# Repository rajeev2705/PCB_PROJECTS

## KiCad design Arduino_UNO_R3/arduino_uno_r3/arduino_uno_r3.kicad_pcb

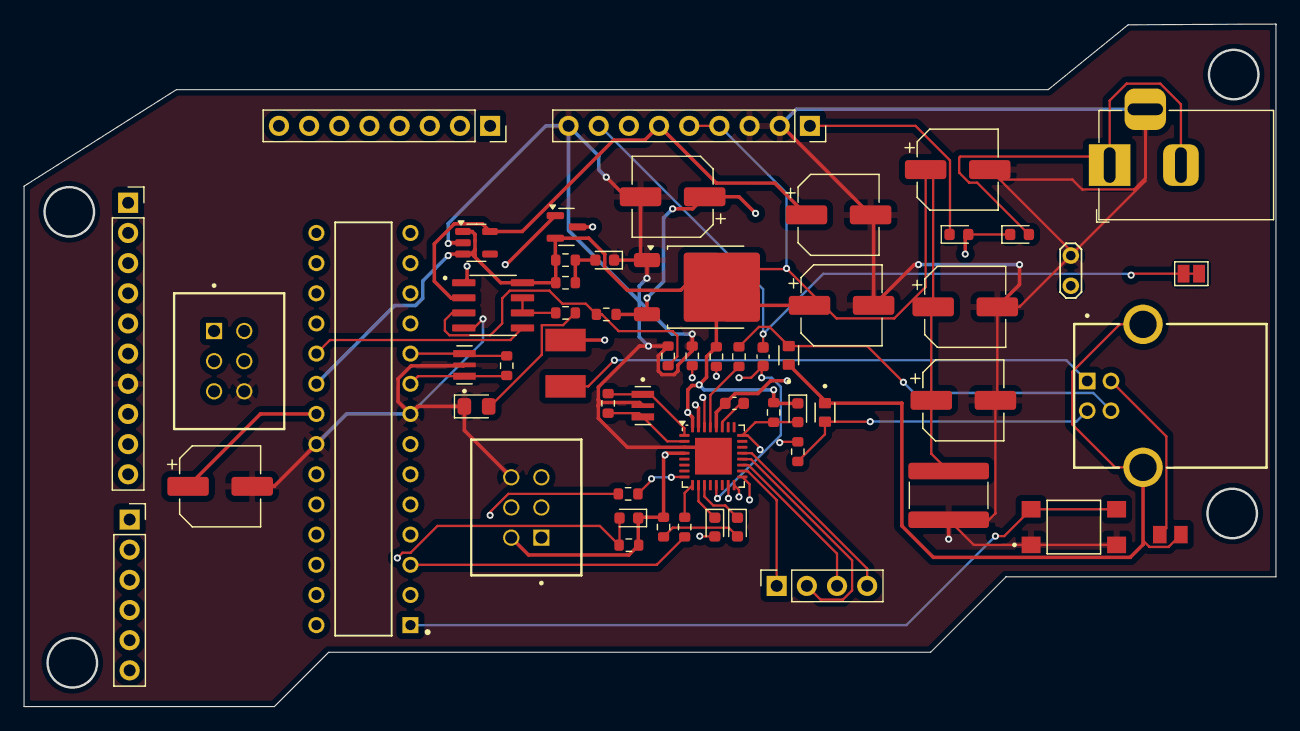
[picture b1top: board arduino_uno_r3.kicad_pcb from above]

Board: 4 copper layers, 105.4 x 57.5 mm, 58 parts (0 on the bottom side), 62 nets.

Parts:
C1, C2: 47u; CP_Elec_6.3x3
C3, C4, C9, C10: 100n; CP_Elec_6.3x3
C5: 1u; CP_Elec_6.3x3
C6: 1u; C_0603_1608Metric
C7: 100n; C_1825_4564Metric
C8: 100n; C_0603_1608Metric
D1, D3, D7, D8: D; D_0603_1608Metric
D2: GREEN ON; LED_0603_1608Metric
D4, D5: LED; LED_0603_1608Metric
D6: LED; LED_0805_2012Metric_Pad1.15x1.40mm_HandSolder
F1: MF-MSMF050-2; FUSM1812X02
FL1: BLM21SP111SH1D; BEADC2012X105N
J1: Barrel_Jack_Switch_Pin3Ring; BarrelJack_Horizontal
J2: Conn_01x09_Socket; PinSocket_1x09_P2.54mm_Vertical
J3: USB-B-S-X-X-TH-TR; SAMTEC_USB-B-S-X-X-TH-TR
J4, J6: ICSP HEADER; SAMTEC_TSS-103-03-L-D
J5: Conn_01x04_Socket; PinSocket_1x04_P2.54mm_Vertical
J7: Conn_01x08_Socket; PinSocket_1x08_P2.54mm_Vertical
J8: Conn_01x10_Socket; PinSocket_1x10_P2.54mm_Vertical
J9: Conn_01x06_Socket; PinSocket_1x06_P2.54mm_Vertical
JP1: SolderJumper_2_Open; SolderJumper-2_P1.3mm_Open_Pad1.0x1.5mm
JP2: SolderJumper_2_Open; TestPoint_2Pads_Pitch2.54mm_Drill0.8mm
Q1: FDN340P; SOT-23
R1A1, R1B1, R8, R9, R11, R12, R15, R16: 1k; R_0603_1608Metric
R3, R4, R5, R14: 10k; R_0603_1608Metric
R6, R7: 22R; R_0603_1608Metric
R10, R13: 1M; R_0603_1608Metric
RV1, RV2: CG0603MLC-05E; VARC1608X56N
S1: TL3305CF160QG; SW_TL3305CF160QG
U1: NCP1117-5.0_TO252; TO-252-2
U3: LP2985-3.3; SOT-23-5
U4: ATmega16U2-M; QFN-32-1EP_5x5mm_P0.5mm_EP3.1x3.1mm
U6: LMV358; SOIC127P599X175-8N
U7: ATMEGA328P-PU; DIP794W46P254L2967H457Q28B
Y1, Y2: CSTCE16M0V53-R0; OSC_CSTCE16M0V53-R0

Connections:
+5V: C2.1, C3.1, C4.1, C7.2, C10.1, D3.1 (K), D7.1 (K), J2.4, J2.5, J4.02, J6.02, Q1.2 (S), R1A1.2, R1B1.2, R5.2, R8.1, R9.1, R14.2, U1.2 (VO), U3.1 (VIN), U3.3 (ON/~OFF), U4.4 (VCC), U4.32 (AVCC), U6.8 (V+), U7.7 (VCC), U7.20 (AVCC)
/MCU/AREF: C9.1, J8.8, U7.21 (AREF)
/MCU/IO0/RXD: J7.1, R15.1, U7.2 (PD0)
/MCU/IO1/TXD: J7.2, R16.1, U7.3 (PD1)
/MCU/IO2: J7.3, U7.4 (PD2)
/MCU/IO3: J7.4, U7.5 (PD3)
/MCU/IO4: J7.5, U7.6 (PD4)
/MCU/IO5: J7.6, U7.11 (PD5)
/MCU/IO6: J7.7, U7.12 (PD6)
/MCU/IO7: J7.8, U7.13 (PD7)
/MCU/IO8: J8.1, U7.14 (PB0)
/MCU/IO9: J8.2, U7.15 (PB1)
/MCU/PB3/MOSI: J6.04, J8.4, U7.17 (PB3)
/MCU/PB4/MISO: J6.01, J8.5, U7.18 (PB4)
/MCU/PB5/SCK: J6.03, J8.6, U6.5 (+), U7.19 (PB5)
/MCU/PC0: J9.1, U7.23 (PC0)
/MCU/PC1: J9.2, U7.24 (PC1)
/MCU/PC2: J9.3, U7.25 (PC2)
/MCU/PC3: J9.4, U7.26 (PC3)
/MCU/PC4/SDA: J8.9, J9.5, U7.27 (PC4)
/MCU/PC5/SCL: J8.10, J9.6, U7.28 (PC5)
/MCU/RESET: D7.2 (A), J6.05, R14.1, S1.3, S1.4, U7.1 (PC6/~RESET)
/MCU/SS: J8.3, U7.16 (PB2)
/POWER SEC/+3.3V: C5.1, J2.6, U3.5 (VOUT), U6.2 (-)
/POWER SEC/GATE_CONTROL: Q1.1 (G), U6.1
/POWER SEC/PWRIN: D1.2 (A), J1.1, J1.2
/POWER SEC/VIN: C1.1, D1.1 (K), D8.2 (A), J2.7, R3.1, U1.3 (VI)
/USB SECTION/AT_TO_CAP: C6.1, U4.27 (UCAP)
/USB SECTION/MCUD+: R7.1, U4.29 (D+)
/USB SECTION/MCUD-: R6.1, U4.30 (D-)
/USB SECTION/MISO2: J4.01, U4.17 (PB3)
/USB SECTION/MOSI2: J4.04, U4.16 (PB2)
/USB SECTION/PB4: J5.1, U4.18 (PB4)
/USB SECTION/PB5: J5.3, U4.19 (PB5)
/USB SECTION/PB6: J5.2, U4.20 (PB6)
/USB SECTION/PB7: J5.4, U4.21 (PB7)
/USB SECTION/PD7: C8.2, R11.2, U4.13 (~HWB/PD7)
/USB SECTION/RESET2: D3.2 (A), J4.05, R5.1, U4.24 (PC1/~RESET)
/USB SECTION/SCK2: J4.03, U4.15 (PB1)
/USB SECTION/USBD+: J3.3 (D+), R7.2, RV2.2
/USB SECTION/USBD-: J3.2 (D-), R6.2, RV1.2
/USB SECTION/USBGND: C6.2, FL1.2, J3.4 (GND), JP2.1 (A), U4.28 (UGND)
/USB SECTION/USBSHIELD: FL1.1, J3.S1 (SHIELD), J3.S2 (SHIELD), RV1.1, RV2.1
GND: C1.2, C2.2, C3.2, C4.2, C5.2, C7.1, C9.2, C10.2, D2.1 (K), D6.1 (K), J1.3, J2.2, J2.3, J2.9, J4.06, J6.06, J8.7, JP2.2 (B), R4.1, R11.1, S1.1, S1.2, U1.1 (GND), U3.2 (GND), U4.3 (GND), U4.33 (GND), U6.4 (V-), U7.8 (GND), U7.22 (GND), Y1.2, Y2.2
unnamed: D2.2 (A), R1A1.1, R1B1.1
unnamed: D4.2 (A), R8.2
unnamed: D5.2 (A), R9.2
unnamed: D6.2 (A), R12.2
unnamed: D8.1 (K), J2.1
unnamed: F1.1, J3.1 (VCC)
unnamed: R10.2, U4.2 (PC0/XTAL2), Y1.3
unnamed: R10.1, U4.1 (XTAL1), Y1.1
unnamed: R3.2, R4.2, U6.3 (+)
unnamed: R12.1, U6.6 (-), U6.7
unnamed: R13.1, U7.9 (PB6), Y2.1
unnamed: R13.2, U7.10 (PB7), Y2.3
RESET: C8.1, J2.8, JP1.1 (A), JP1.2 (B)
RXLED: D5.1 (K), U4.10 (PD4)
RXM8: R15.2, U4.8 (PD2)
TXLED: D4.1 (K), U4.11 (PD5)
TXM8: R16.2, U4.9 (PD3)
USBVCC: F1.2, Q1.3 (D), U4.31 (UVCC)

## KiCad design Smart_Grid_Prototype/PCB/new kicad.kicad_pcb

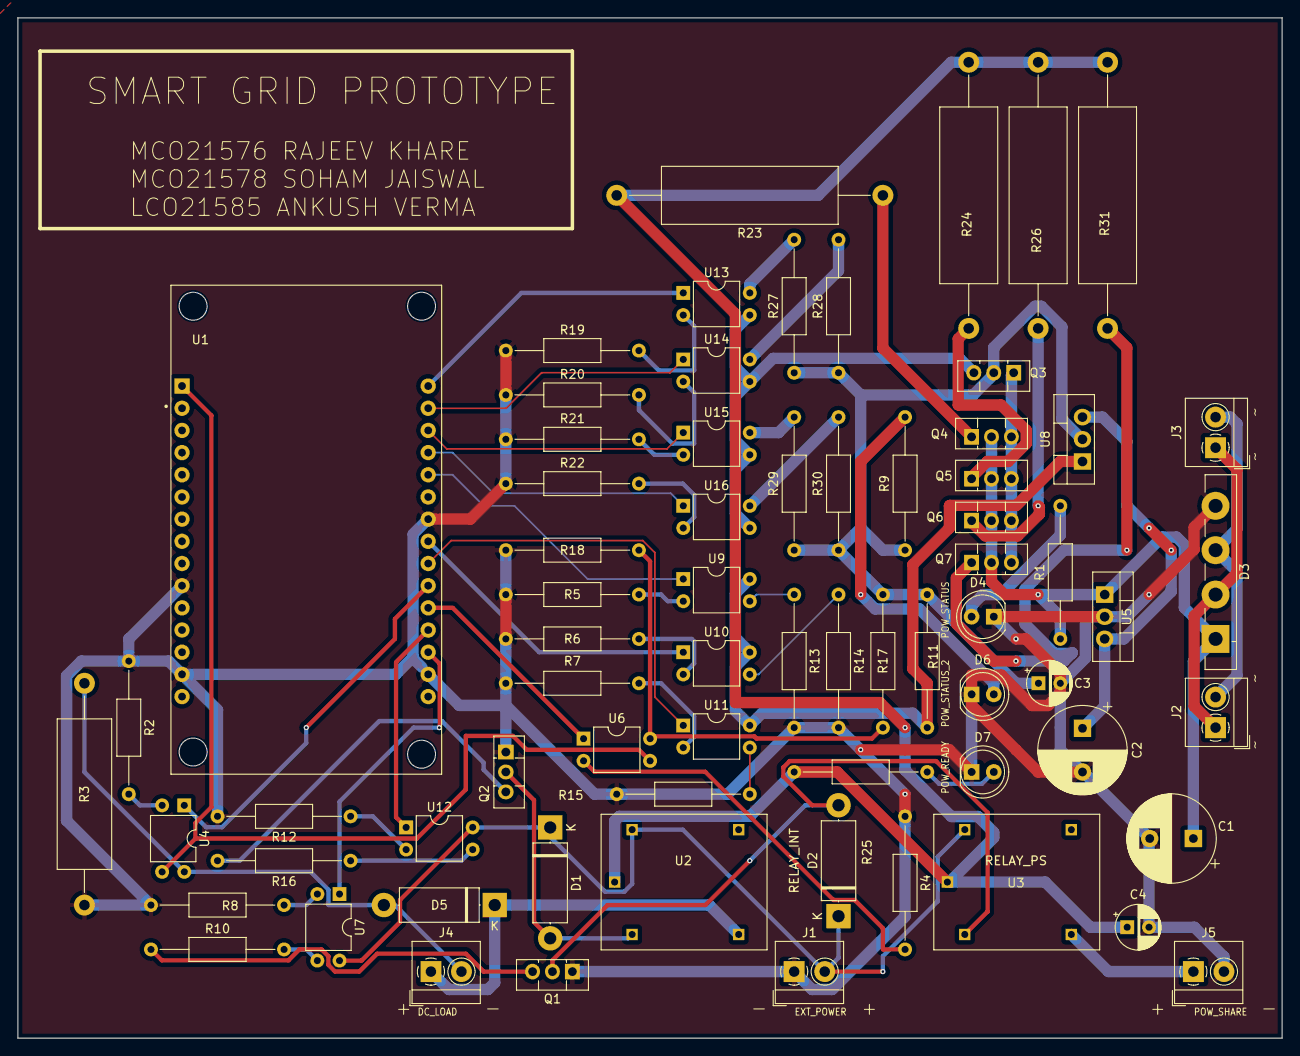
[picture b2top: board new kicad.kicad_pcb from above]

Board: 2 copper layers, 144.8 x 116.8 mm, 70 parts (0 on the bottom side), 58 nets.

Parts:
C1: 1000uf/25V; CP_Radial_D10.0mm_P5.00mm
C2: 100uf/25V; CP_Radial_D10.0mm_P5.00mm
C3, C4: 10uF/63V; CP_Radial_D5.0mm_P2.50mm
D1, D2: 1N5408/DIODE; D_5W_P12.70mm_Horizontal
D3: GBU4A/BRIDGE_RECT; Diode_Bridge_Vishay_GBU
D4: LED_POW; LED_D5.0mm
D5: 1N5408/FWD; D_5W_P12.70mm_Horizontal
D6: LED; LED_D5.0mm
D7: LOAD_STATUS; LED_D5.0mm
J1: EXT_POW; TerminalBlock_4Ucon_1x02_P3.50mm_Horizontal
J2: 24VAC _LOAD; TerminalBlock_4Ucon_1x02_P3.50mm_Horizontal
J3: AC_INPUT; TerminalBlock_4Ucon_1x02_P3.50mm_Horizontal
J4: DC_LOAD; TerminalBlock_4Ucon_1x02_P3.50mm_Horizontal
J5: POW_SHARE; TerminalBlock_4Ucon_1x02_P3.50mm_Horizontal
Q1, Q2, Q3, Q4, Q5, Q6, Q7: BD139; TO-126-3_Vertical
R1, R19, R20, R21, R22, R25: 220; R_Axial_DIN0207_L6.3mm_D2.5mm_P15.24mm_Horizontal
R2, R4, R5, R6, R7, R8, R9, R11, R12: 220R; R_Axial_DIN0207_L6.3mm_D2.5mm_P15.24mm_Horizontal
R3: 1R; R_Axial_DIN0617_L17.0mm_D6.0mm_P25.40mm_Horizontal
R10, R16: 120R; R_Axial_DIN0207_L6.3mm_D2.5mm_P15.24mm_Horizontal
R13: 500R; R_Axial_DIN0207_L6.3mm_D2.5mm_P15.24mm_Horizontal
R14: 1.5k; R_Axial_DIN0207_L6.3mm_D2.5mm_P15.24mm_Horizontal
R15: 2k; R_Axial_DIN0207_L6.3mm_D2.5mm_P15.24mm_Horizontal
R17: 20k; R_Axial_DIN0207_L6.3mm_D2.5mm_P15.24mm_Horizontal
R18: 8k; R_Axial_DIN0207_L6.3mm_D2.5mm_P15.24mm_Horizontal
R23, R24, R26, R31: 1R; R_Axial_Power_L20.0mm_W6.4mm_P30.48mm
R27: 150R; R_Axial_DIN0207_L6.3mm_D2.5mm_P15.24mm_Horizontal
R28: 1k; R_Axial_DIN0207_L6.3mm_D2.5mm_P15.24mm_Horizontal
R29: 3k; R_Axial_DIN0207_L6.3mm_D2.5mm_P15.24mm_Horizontal
R30: 5k; R_Axial_DIN0207_L6.3mm_D2.5mm_P15.24mm_Horizontal
U1: ESP8266; MODULE_ZC563900
U2: RELAY_INT; J107F
U3: RELAY_PS; J107F
U4, U6, U7, U9, U10, U11, U12, U13, U14, U15, U16: PC817; DIP-4_W7.62mm
U5: LM7824_TO220; TO-220-3_Vertical
U8: LM317_TO-220; TO-220-3_Vertical

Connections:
/1k_R: R28.2, U14.4
/3k_R: R29.2, U15.4
/5k_R: R30.2, U16.4
/150_R: R27.2, U13.4
/A0: U1.1 (A0), U4.3, U6.3
/CURRENT_CONTROL: Q3.3 (B), U13.3, U14.3, U15.3, U16.3
/C_SENSE: D5.2 (A), J4.2, R3.1, U4.4
/D0: U1.30 (D0), U13.1
/D1: U1.29 (D1), U14.1
/D2: U1.28 (D2), U15.1
/D3: U1.27 (D3), U16.1
/D4: U1.26 (D4), U9.1
/D5: U1.23 (D5), U10.1
/D6: U1.22 (D6), U11.1
/D7: U1.21 (D7), U4.1
/D8: U1.20 (D8), U6.1
/E1_TO_R: Q4.1 (E), R23.1
/E2_TO_R: Q5.1 (E), R24.1
/E3_TO_R: Q6.1 (E), R26.1
/E4_TO_R: Q7.1 (E), R31.1
/EXT_POWER: D1.1 (K), D2.1 (K), J1.2, U2.P$1, U3.P$1, U7.4, U12.4
/LOAD+: C4.1, R23.2, R24.2, R25.1, R26.2, R31.2, U2.P$2, U3.P$2
/POWER_ON_OFF: U1.19 (RX), U12.1
/POW_IN_CON: C1.1, D3.1 (+), Q4.2 (C), Q5.2 (C), Q6.2 (C), Q7.2 (C), R1.1, U5.1 (VI)
/POW_REG_CON: C2.1, U5.3 (VO), U8.3 (VI)
/PSHARE_ON_OFF: U1.18 (TX), U7.1
/RELAY1_IN: D2.2 (A), Q1.2 (C), U3.P$3
/RELAY_IN: D1.2 (A), Q2.2 (C), U2.P$3
/V_CONTROL: R11.1, U8.1 (ADJ), U9.4, U10.4, U11.4
/V_OUT: C3.1, Q3.2 (C), R9.1, R11.2, R17.1, R27.1, R28.1, R29.1, R30.1, U8.2 (VO)
/V_SENSE: R17.2, R18.1, U6.4
GND: C1.2, C2.2, C3.2, C4.2, D3.4 (-), D4.1 (K), D6.1 (K), D7.1 (K), J1.1, J5.2, Q1.1 (E), Q2.1 (E), R2.1, R3.2, R4.1, R5.1, R6.1, R7.1, R8.2, R12.2, R13.2, R14.2, R15.2, R18.2, R19.1, R20.1, R21.1, R22.1, U1.10 (GND), U1.14 (GND), U1.17 (GND), U1.24 (GND), U5.2 (GND)
unnamed: D4.2 (A), R1.2
unnamed: D5.1 (K), J4.1, U2.P$4
unnamed: D6.2 (A), R9.2
unnamed: D7.2 (A), R25.2
unnamed: D3.2, J2.1, J3.1
unnamed: J5.1, U3.P$4
unnamed: Q1.3 (B), R10.1
unnamed: Q2.3 (B), R16.2
unnamed: Q3.1 (E), Q4.3 (B), Q5.3 (B), Q6.3 (B), Q7.3 (B)
unnamed: R2.2, U4.2
unnamed: R4.2, U6.2
unnamed: R5.2, U9.2
unnamed: R6.2, U10.2
unnamed: R7.2, U11.2
unnamed: R8.1, U7.2
unnamed: R10.2, U7.3
unnamed: R12.1, U12.2
unnamed: R13.1, U9.3
unnamed: R14.1, U10.3
unnamed: R15.1, U11.3
unnamed: R16.1, U12.3
unnamed: R19.2, U13.2
unnamed: R20.2, U14.2
unnamed: R21.2, U15.2
unnamed: R22.2, U16.2
VAC: D3.3, J2.2, J3.2
